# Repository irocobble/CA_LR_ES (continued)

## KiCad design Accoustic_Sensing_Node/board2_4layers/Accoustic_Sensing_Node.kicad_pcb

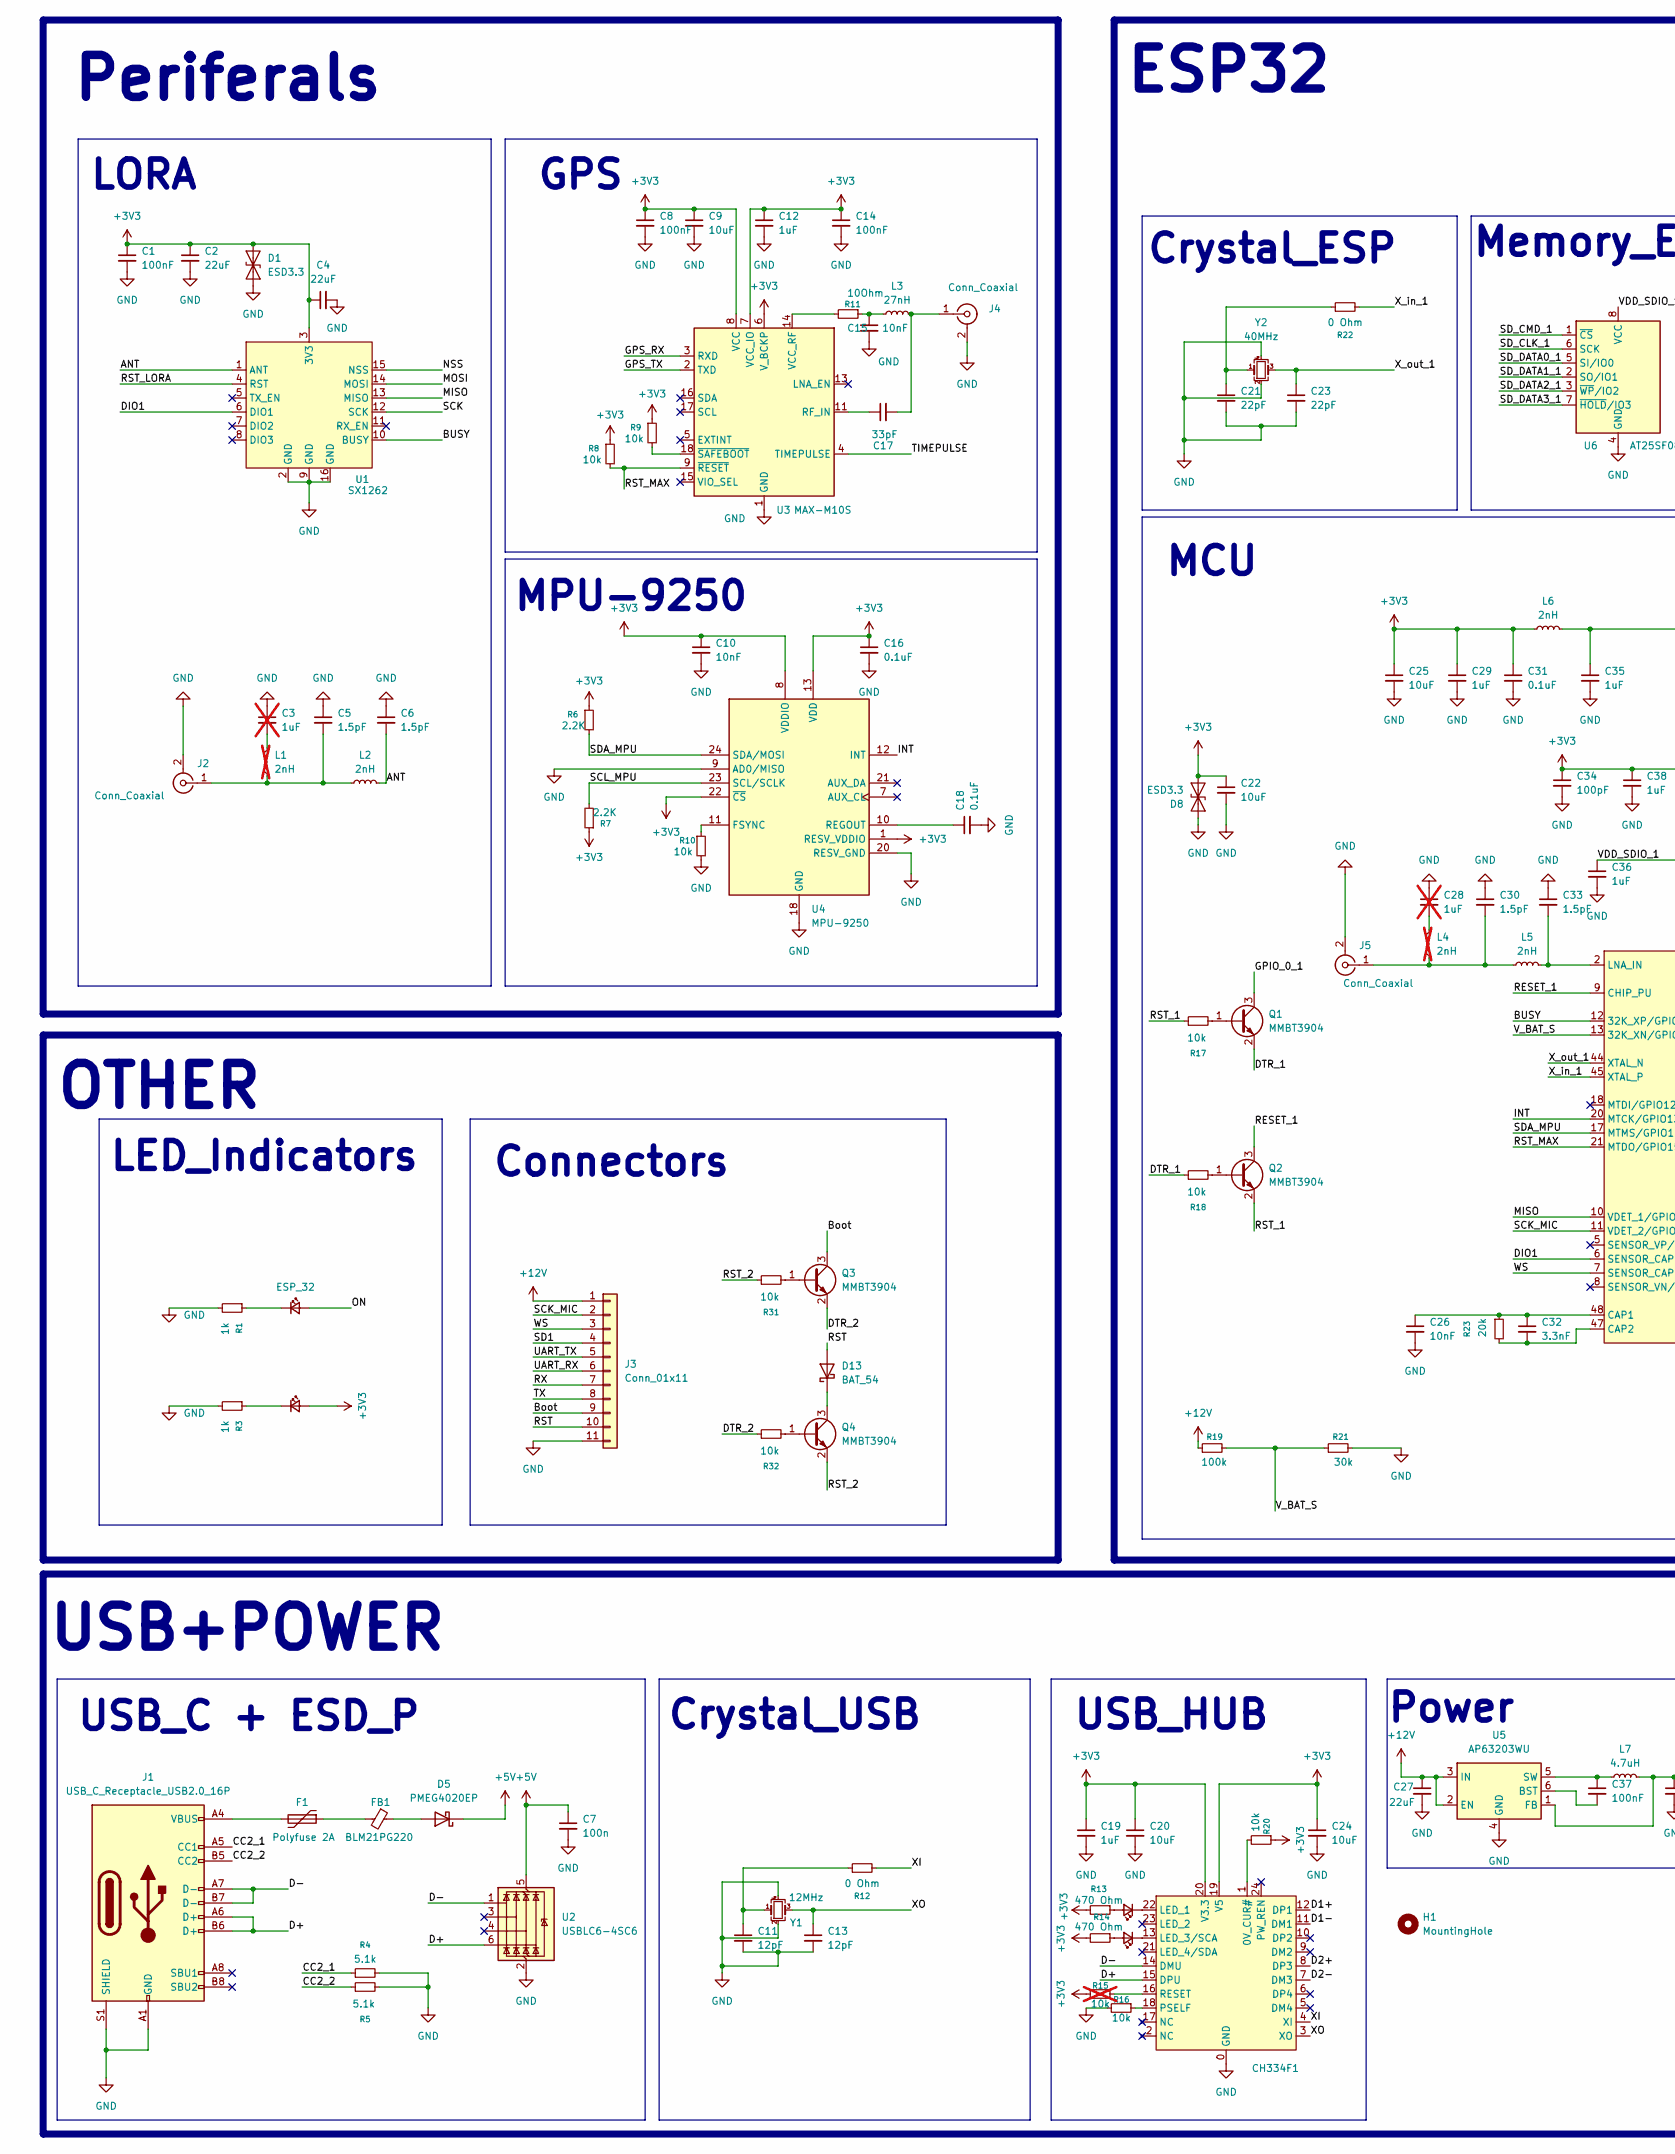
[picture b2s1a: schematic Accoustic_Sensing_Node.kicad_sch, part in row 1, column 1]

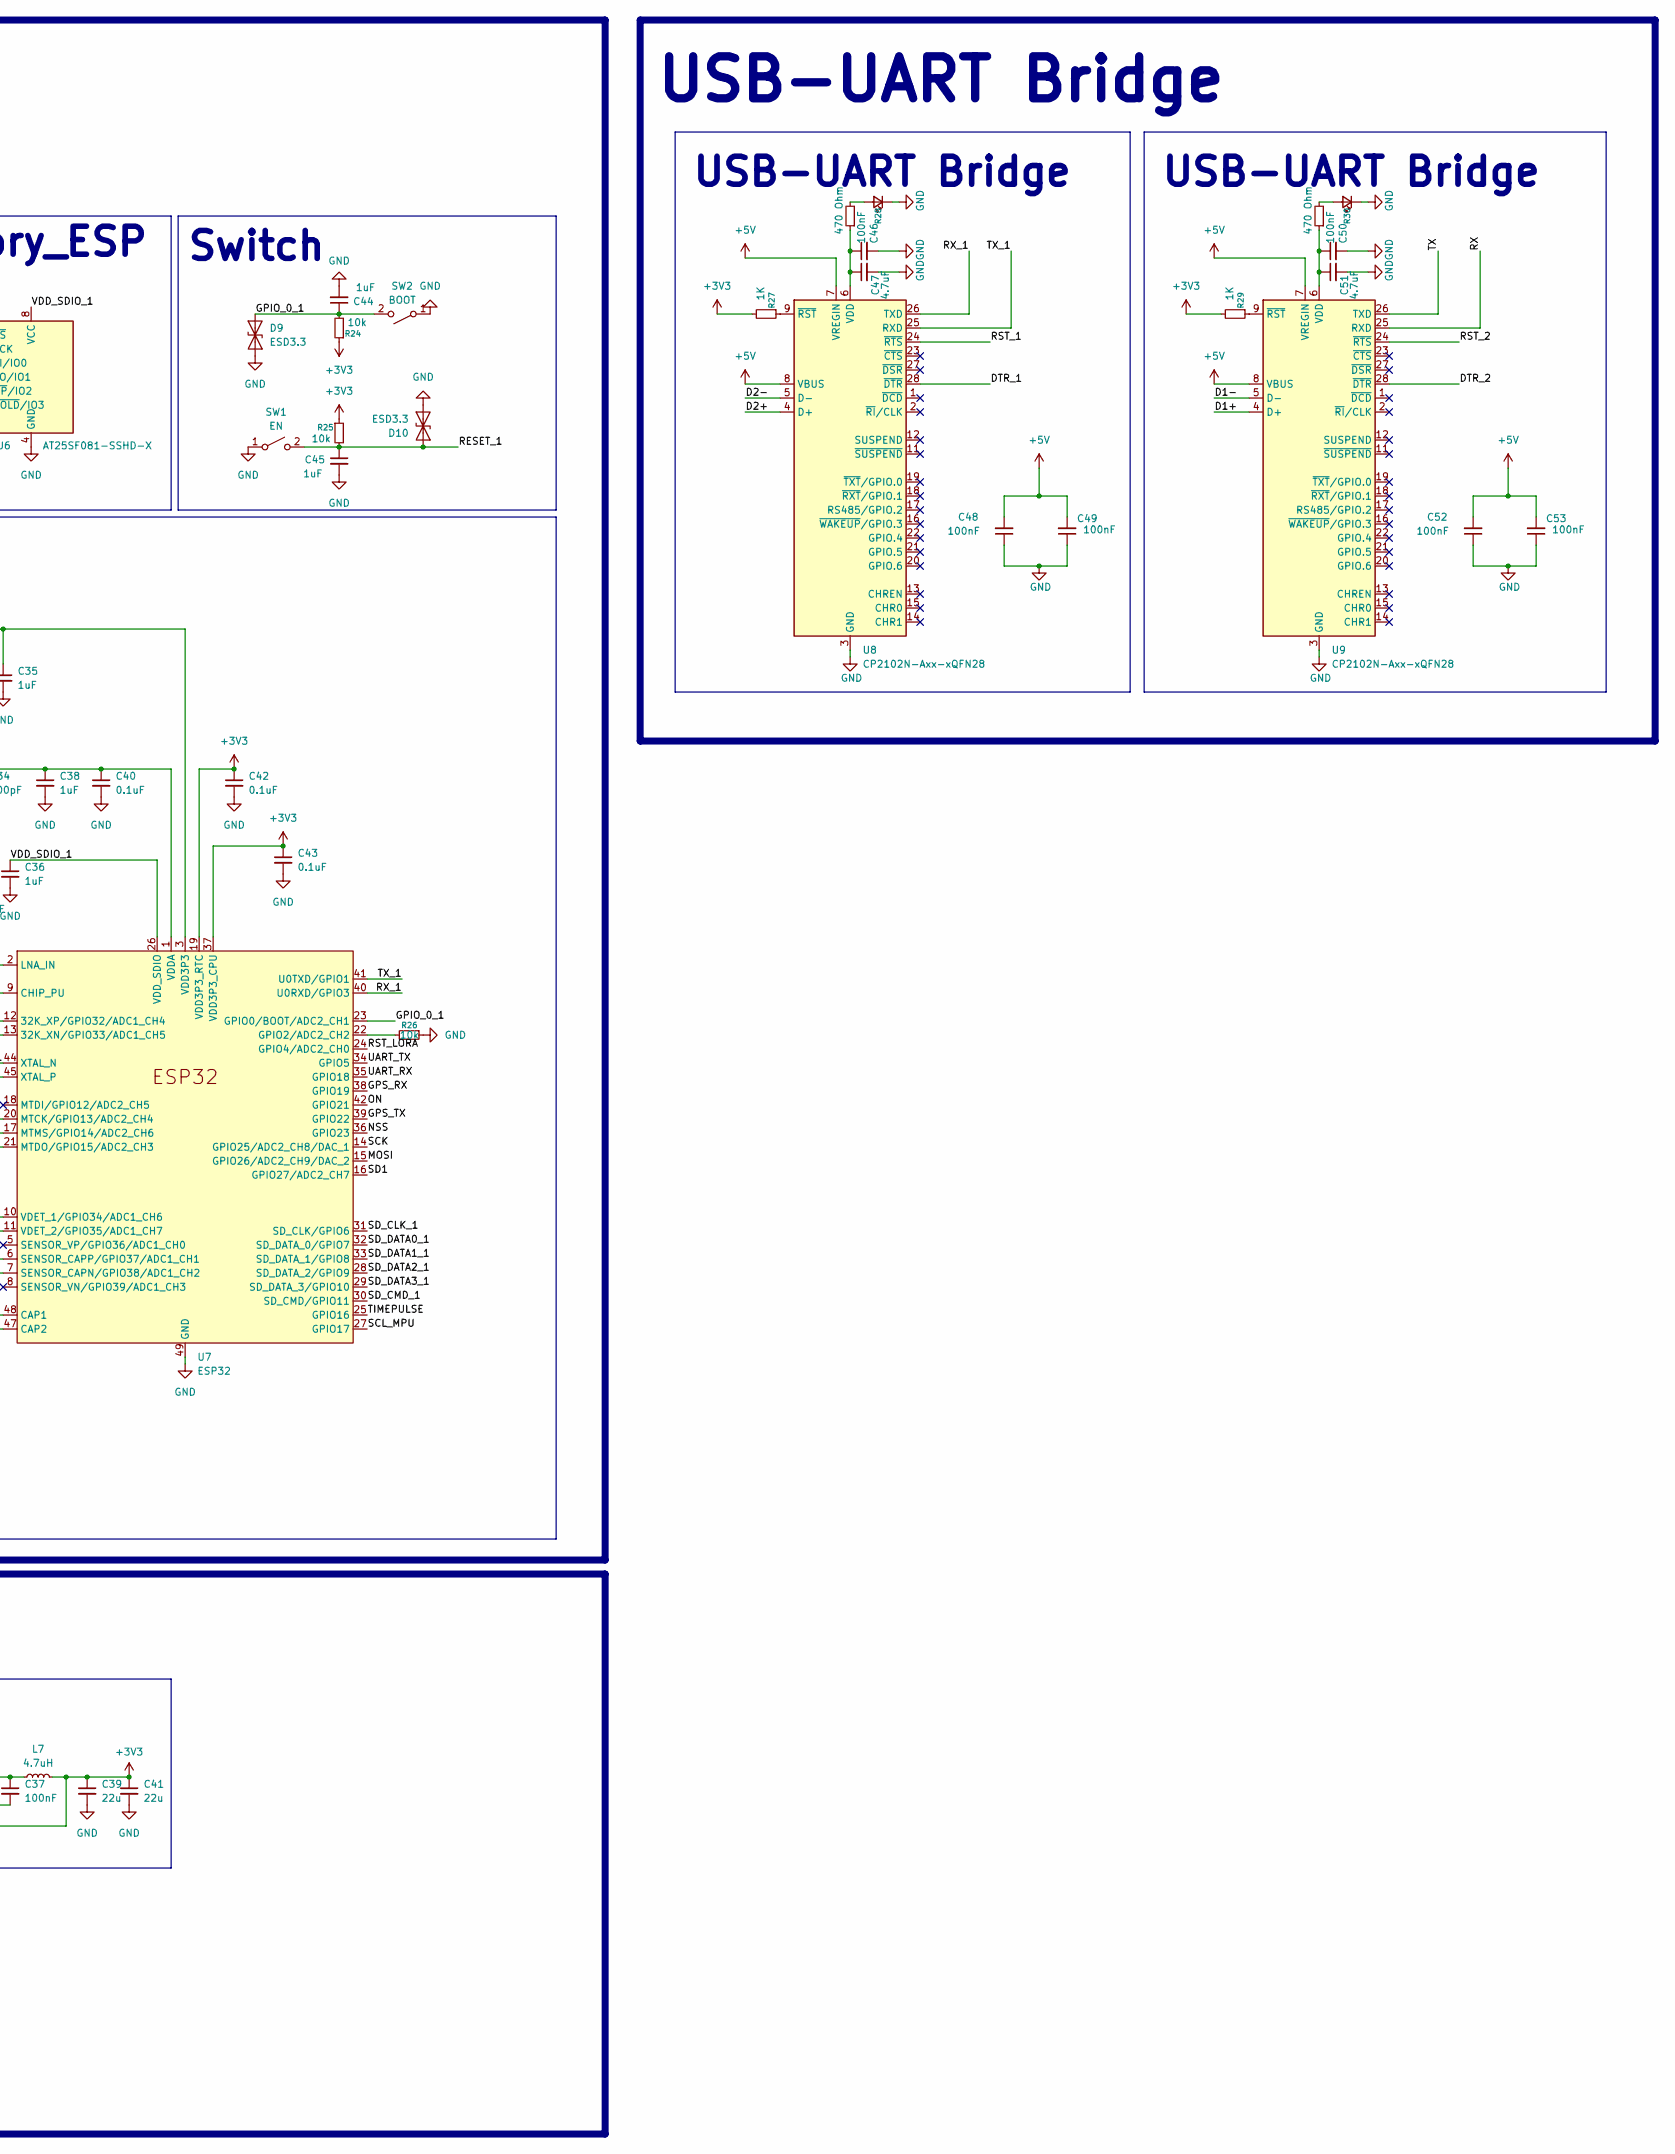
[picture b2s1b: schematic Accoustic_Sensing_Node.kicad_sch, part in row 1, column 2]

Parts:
C1, C8, C14, C37: 100nF; C_0603_1608Metric
C2, C4, C27: 22uF; C_0805_2012Metric
C3, C28: 1uF; C_0603_1608Metric; not fitted
C5, C6, C30, C33: 1.5pF; C_0402_1005Metric
C7: 100n; C_0402_1005Metric
C9, C20, C22, C24: 10uF; C_0805_2012Metric
C10, C15: 10nF; C_0603_1608Metric
C11, C13: 12pF; C_0402_1005Metric
C12: 1uF; C_0402_1005Metric
C16, C18, C31, C40, C42, C43: 0.1uF; C_0402_1005Metric
C17: 33pF; C_0402_1005Metric
C19, C29, C35, C36, C38, C44, C45: 1uF; C_0603_1608Metric
C21, C23: 22pF; C_0402_1005Metric
C25: 10uF; C_0805_2012Metric_Pad1.18x1.45mm_HandSolder
C26: 10nF; C_0402_1005Metric
C32: 3.3nF; C_0402_1005Metric
C34: 100pF; C_0402_1005Metric
C39, C41: 22u; C_0805_2012Metric
C46, C48, C49, C50, C52, C53: 100nF; C_0402_1005Metric
C47, C51: 4.7uF; C_0805_2012Metric
CH334F1: QFN24_4MM
D1, D8, D9, D10: ESD3.3; D_SOD-523
D2: ESP_32; LED_0805_2012Metric
D4: Power; LED_0805_2012Metric
D5: PMEG4020EP; D_SOD-123F
D6: USB1; LED_0805_2012Metric
D7: USB2; LED_0805_2012Metric
D11, D12: UART1_ON; LED_0805_2012Metric
D13: BAT_54; SOT-23
F1: Polyfuse 2A; Fuse_1206_3216Metric
FB1: BLM21PG220; L_0805_2012Metric
H1: MountingHole; MountingHole_2.7mm_M2.5_Pad_TopBottom
J1: USB_C_Receptacle_USB2.0_16P; USB_C_Receptacle_HCTL_HC-TYPE-C-16P-01A
J2, J4, J5: Conn_Coaxial; U.FL_Hirose_U.FL-R-SMT-1_Vertical
J3: Conn_01x11; Castellated_Edge_11P_2.54
L1, L4: 2nH; L_0402_1005Metric; not fitted
L2, L5, L6: 2nH; L_0402_1005Metric
L3: 27nH; L_0402_1005Metric
L7: 4.7uH; L_Sunlord_SWPA6020S
Q1, Q2, Q3, Q4: MMBT3904; SOT-23
R1, R3: 1k; R_0402_1005Metric
R4, R5: 5.1k; R_0402_1005Metric
R6, R7: 2.2K; R_0402_1005Metric
R8, R9, R10, R16, R17, R18, R20, R24, R25, R26, R31, R32: 10k; R_0402_1005Metric
R11: 10Ohm; R_0805_2012Metric
R12, R22: 0 Ohm; R_0402_1005Metric
R13, R14, R28, R30: 470 Ohm; R_0402_1005Metric
R15: 10k; R_0402_1005Metric; not fitted
R19: 100k; R_0402_1005Metric
R21: 30k; R_0402_1005Metric
R23: 20k; R_0402_1005Metric
R27, R29: 1K; R_0402_1005Metric
SW1: EN; SW_CS1213AGF260_CRS
SW2: BOOT; SW_CS1213AGF260_CRS
U1: SX1262; SX1262-B
U2: USBLC6-4SC6; SOT-23-6
U3: MAX-M10S; ublox_MAX
U4: MPU-9250; InvenSense_QFN-24_3x3mm_P0.4mm
U5: AP63203WU; TSOT-23-6
U6: AT25SF081-SSHD-X; SOIC-8_3.9x4.9mm_P1.27mm
U7: ESP32; QFN-48-1EP_5x5mm_P0.35mm_EP3.7x3.7mm
U8, U9: CP2102N-Axx-xQFN28; QFN-28-1EP_5x5mm_P0.5mm_EP3.35x3.35mm
Y1: 12MHz; Crystal_SMD_3225-4Pin_3.2x2.5mm
Y2: 40MHz; Crystal_SMD_3225-4Pin_3.2x2.5mm

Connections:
+3V3: C1.1, C2.1, C4.1, C8.1, C9.1, C10.1, C12.1, C14.1, C16.1, C19.1, C20.1, C22.1, C24.1, C25.1, C29.1, C31.1, C34.1, C38.1, C39.1, C40.1, C41.1, C42.1, C43.1, CH334F1.19 (V5), CH334F1.20 (V3.3), D1.2 (A2), D4.2 (A), D8.1 (A1), L6.1, L7.2, R6.1, R7.1, R8.1, R9.1, R13.2, R14.2, R15.2, R20.1, R24.1, R25.1, R27.2, R29.2, U1.3 (3V3), U3.6 (V_BCKP), U3.7 (VCC_IO), U3.8 (VCC), U4.1 (RESV_VDDIO), U4.8 (VDDIO), U4.13 (VDD), U4.22 (~CS), U5.1 (FB), U7.1 (VDDA), U7.19 (VDD3P3_RTC), U7.37 (VDD3P3_CPU), U7.43 (VDDA), U7.46 (VDDA)
+5V: C7.1, C48.2, C49.2, C52.2, C53.2, D5.1 (K), U2.5 (VBUS), U8.7 (VREGIN), U8.8 (VBUS), U9.7 (VREGIN), U9.8 (VBUS)
+12V: C27.1, J3.1, R19.1, U5.2 (EN), U5.3 (IN)
/ANT: C6.2, L2.2, U1.1 (ANT)
/BUSY: U1.10 (BUSY), U7.12 (32K_XP/GPIO32/ADC1_CH4)
/Boot: J3.9, Q3.3 (C)
/CC2_1: J1.A5 (CC1), R4.1
/CC2_2: J1.B5 (CC2), R5.1
/D1+: CH334F1.12 (DP1), U9.4 (D+)
/D1-: CH334F1.11 (DM1), U9.5 (D-)
/D2+: CH334F1.8 (DP3), U8.4 (D+)
/D2-: CH334F1.7 (DM3), U8.5 (D-)
/D+: CH334F1.15 (DPU), J1.A6 (D+), J1.B6 (D+), U2.6 (I/O4)
/D-: CH334F1.14 (DMU), J1.A7 (D-), J1.B7 (D-), U2.1 (I/O1)
/DIO1: U1.6 (DIO1), U7.6 (SENSOR_CAPP/GPIO37/ADC1_CH1)
/DTR_1: Q1.2 (E), R18.1, U8.28 (~DTR)
/DTR_2: Q3.2 (E), R32.1, U9.28 (~DTR)
/GPIO_0_1: C44.1, D9.2 (A2), Q1.3 (C), R24.2, SW2.2 (B), U7.23 (GPIO0/BOOT/ADC2_CH1)
/GPS_RX: U3.3 (RXD), U7.38 (GPIO19)
/GPS_TX: U3.2 (TXD), U7.39 (GPIO22)
/INT: U4.12 (INT), U7.20 (MTCK/GPIO13/ADC2_CH4)
/MISO: U1.13 (MISO), U7.10 (VDET_1/GPIO34/ADC1_CH6)
/MOSI: U1.14 (MOSI), U7.15 (GPIO26/ADC2_CH9/DAC_2)
/NSS: U1.15 (NSS), U7.36 (GPIO23)
/ON: D2.2 (A), U7.42 (GPIO21)
/RESET_1: C45.1, D10.2 (A2), Q2.3 (C), R25.2, SW1.2 (B), U7.9 (CHIP_PU)
/RST: D13.2 (A), J3.10
/RST_1: Q2.2 (E), R17.1, U8.24 (~RTS)
/RST_2: Q4.2 (E), R31.1, U9.24 (~RTS)
/RST_LORA: U1.4 (RST), U7.24 (GPIO4/ADC2_CH0)
/RST_MAX: R8.2, U3.9 (~RESET), U7.21 (MTDO/GPIO15/ADC2_CH3)
/RX: J3.7, U9.25 (RXD)
/RX_1: U7.40 (U0RXD/GPIO3), U8.26 (TXD)
/SCK: U1.12 (SCK), U7.14 (GPIO25/ADC2_CH8/DAC_1)
/SCK_MIC: J3.2, U7.11 (VDET_2/GPIO35/ADC1_CH7)
/SCL_MPU: R7.2, U4.23 (SCL/SCLK), U7.27 (GPIO17)
/SD1: J3.4, U7.16 (GPIO27/ADC2_CH7)
/SDA_MPU: R6.2, U4.24 (SDA/MOSI), U7.17 (MTMS/GPIO14/ADC2_CH6)
/SD_CLK_1: U6.6 (SCK), U7.31 (SD_CLK/GPIO6)
/SD_CMD_1: U6.1 (~CS), U7.30 (SD_CMD/GPIO11)
/SD_DATA0_1: U6.5 (SI/IO0), U7.32 (SD_DATA_0/GPIO7)
/SD_DATA1_1: U6.2 (SO/IO1), U7.33 (SD_DATA_1/GPIO8)
/SD_DATA2_1: U6.3 (~WP/IO2), U7.28 (SD_DATA_2/GPIO9)
/SD_DATA3_1: U6.7 (~HOLD/IO3), U7.29 (SD_DATA_3/GPIO10)
/TIMEPULSE: U3.4 (TIMEPULSE), U7.25 (GPIO16)
/TX: J3.8, U9.26 (TXD)
/TX_1: U7.41 (U0TXD/GPIO1), U8.25 (RXD)
/UART_RX: J3.6, U7.35 (GPIO18)
/UART_TX: J3.5, U7.34 (GPIO5)
/VDD_SDIO_1: C36.1, U6.8 (VCC), U7.26 (VDD_SDIO)
/V_BAT_S: R19.2, R21.1, U7.13 (32K_XN/GPIO33/ADC1_CH5)
/WS: J3.3, U7.7 (SENSOR_CAPN/GPIO38/ADC1_CH2)
/XI: CH334F1.4 (XI), R12.2
/XO: C13.1, CH334F1.3 (XO), Y1.3
/X_in_1: R22.2, U7.45 (XTAL_P)
/X_out_1: C23.1, U7.44 (XTAL_N), Y2.3
GND: C1.2, C2.2, C3.1, C4.2, C5.1, C6.1, C7.2, C8.2, C9.2, C10.2, C11.2, C12.2, C13.2, C14.2, C15.2, C16.2, C18.2, C19.2, C20.2, C21.2, C22.2, C23.2, C24.2, C25.2, C26.2, C27.2, C28.1, C29.2, C30.1, C31.2, C33.1, C34.2, C35.2, C36.2, C38.2, C39.2, C40.2, C41.2, C42.2, C43.2, C44.2, C45.2, C46.2, C47.2, C48.1, C49.1, C50.2, C51.2, C52.1, C53.1, CH334F1.0 (GND), D1.1 (A1), D8.2 (A2), D9.1 (A1), D10.1 (A1), D11.1 (K), D12.1 (K), J1.A1 (GND), J1.A12 (GND), J1.B1 (GND), J1.B12 (GND), J1.S1 (SHIELD), J2.2 (Ext), J3.11, J4.2 (Ext), J5.2 (Ext), R1.2, R3.2, R4.2, R5.2, R10.2, R16.2, R21.2, R26.1, SW1.1 (A), SW2.1 (A), U1.2 (GND), U1.9 (GND), U1.16 (GND), U2.2 (GND), U3.1 (GND), U3.10 (GND), U3.12 (GND), U4.9 (AD0/MISO), U4.18 (GND), U4.20 (RESV_GND), U5.4 (GND), U6.4 (GND), U7.49 (GND), U8.3 (GND), U8.29 (GND), U9.3 (GND), U9.29 (GND), Y1.2, Y1.4, Y2.2, Y2.4
unnamed: C3.2, L1.2
unnamed: C11.1, R12.1, Y1.1
unnamed: C15.1, L3.1, R11.1
unnamed: C21.1, R22.1, Y2.1
unnamed: C28.2, L4.2
unnamed: C35.1, L6.2, U7.3 (VDD3P3), U7.4 (VDD3P3)
unnamed: CH334F1.1 (0V_CUR#), R20.2
unnamed: CH334F1.22 (LED_1), D6.1 (K)
unnamed: CH334F1.13 (LED_3/SCA), D7.1 (K)
unnamed: CH334F1.18 (PSELF), R16.1
unnamed: CH334F1.16 (RESET), R15.1
unnamed: D2.1 (K), R1.1
unnamed: D4.1 (K), R3.1
unnamed: D5.2 (A), FB1.1
unnamed: D6.2 (A), R13.1
unnamed: D7.2 (A), R14.1
unnamed: D11.2 (A), R28.2
unnamed: D12.2 (A), R30.2
unnamed: D13.1 (K), Q4.3 (C)
unnamed: F1.1, FB1.2
unnamed: F1.2, J1.A4 (VBUS), J1.A9 (VBUS), J1.B4 (VBUS), J1.B9 (VBUS)
unnamed: C5.2, J2.1 (In), L1.1, L2.1
unnamed: C17.2, J4.1 (In), L3.2
unnamed: C30.2, J5.1 (In), L4.1, L5.1
unnamed: Q1.1 (B), R17.2
unnamed: Q2.1 (B), R18.2
unnamed: Q3.1 (B), R31.2
unnamed: Q4.1 (B), R32.2
unnamed: C17.1, U3.11 (RF_IN)
unnamed: R11.2, U3.14 (VCC_RF)
unnamed: R9.2, U3.18 (~SAFEBOOT)
unnamed: R10.1, U4.11 (FSYNC)
unnamed: C18.1, U4.10 (REGOUT)
unnamed: C37.2, U5.6 (BST)
unnamed: C37.1, L7.1, U5.5 (SW)
unnamed: C26.1, C32.1, R23.1, U7.48 (CAP1)
unnamed: C32.2, R23.2, U7.47 (CAP2)
unnamed: R26.2, U7.22 (GPIO2/ADC2_CH2)
unnamed: C33.2, L5.2, U7.2 (LNA_IN)
unnamed: C46.1, C47.1, R28.1, U8.6 (VDD)
unnamed: R27.1, U8.9 (~RST)
unnamed: C50.1, C51.1, R30.1, U9.6 (VDD)
unnamed: R29.1, U9.9 (~RST)

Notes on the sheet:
Switch
OTHER
MPU-9250
Power
MCU
USB-UART Bridge
Crystal_ESP
GPS
USB+POWER
Crystal_USB
ESP32
Memory_ESP
LED_Indicators
USB_HUB
Connectors
USB_C + ESD_P
Periferals
LORA

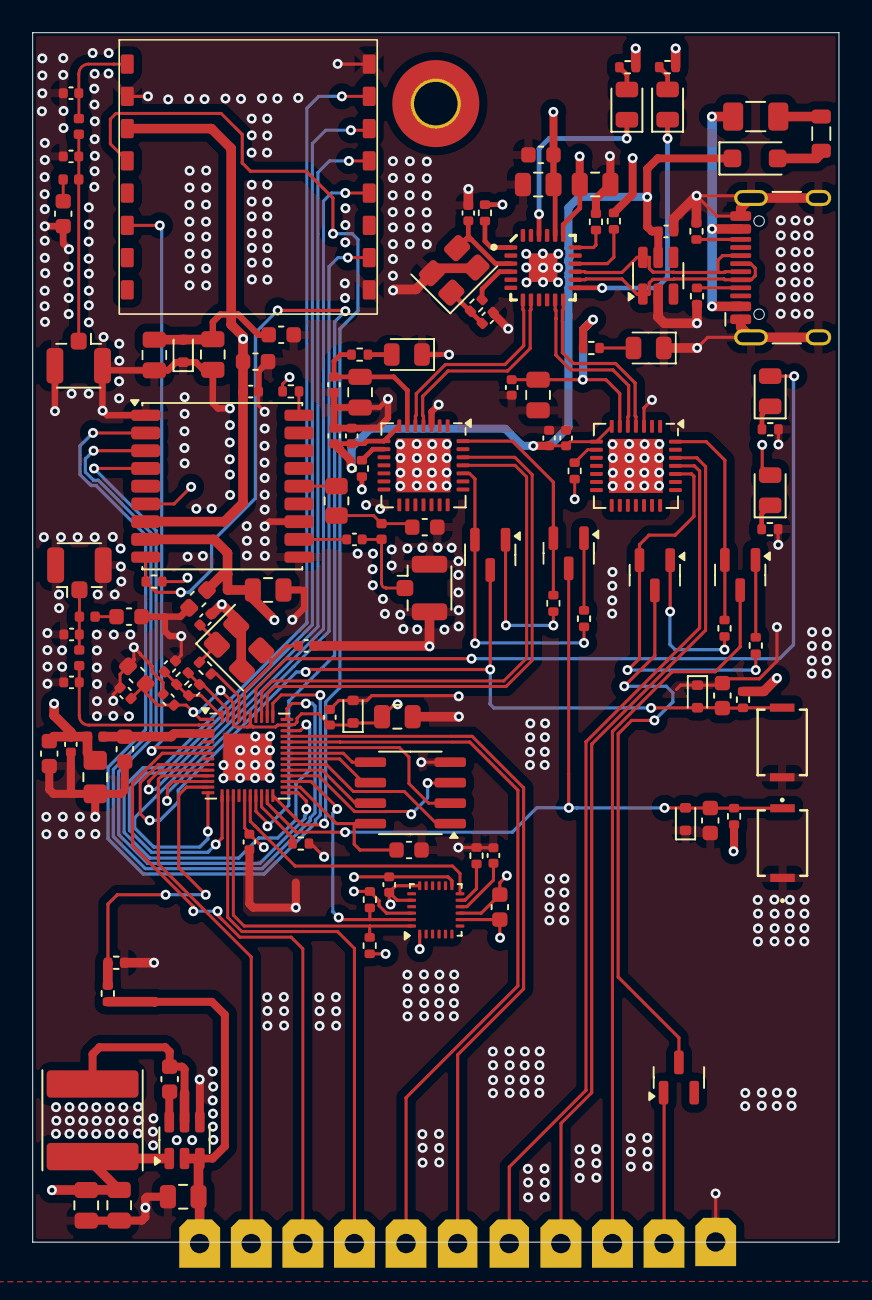
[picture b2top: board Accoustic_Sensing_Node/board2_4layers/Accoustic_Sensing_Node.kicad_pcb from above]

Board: 4 copper layers, 50.0 x 75.0 mm, 129 parts (0 on the bottom side), 100 nets.

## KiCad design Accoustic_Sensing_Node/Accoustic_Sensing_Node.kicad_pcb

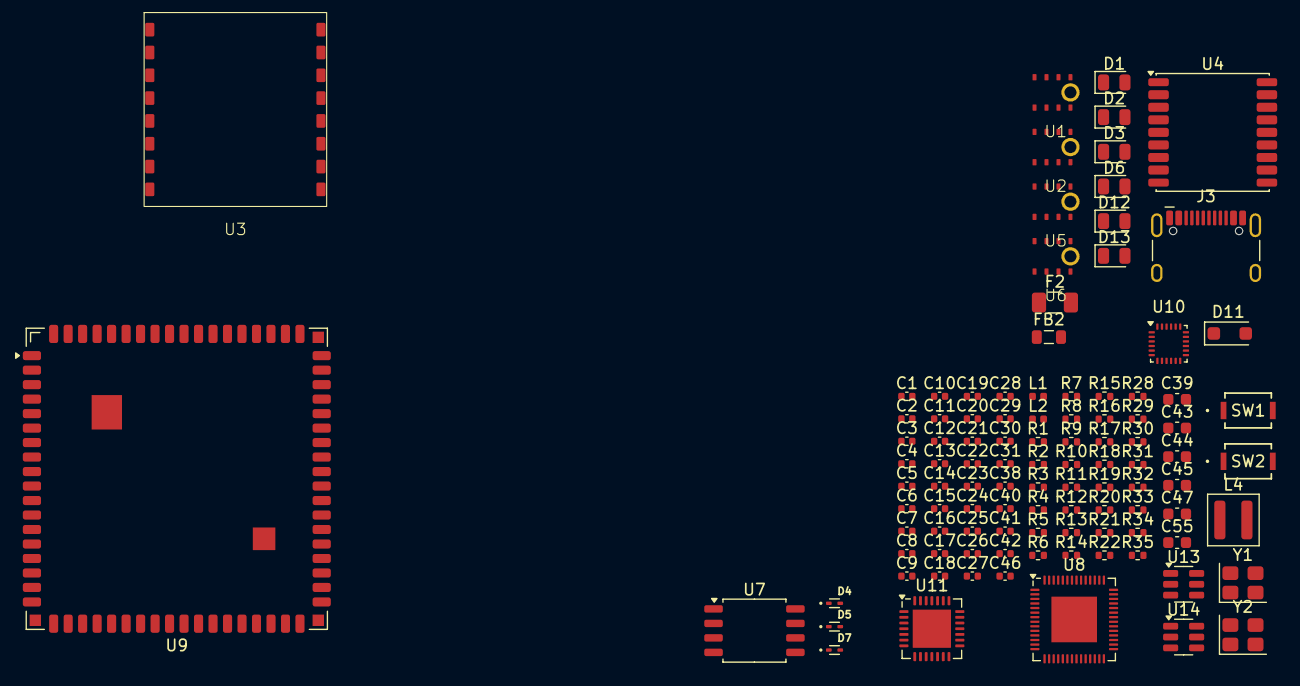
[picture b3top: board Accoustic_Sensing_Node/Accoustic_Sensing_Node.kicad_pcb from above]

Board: 2 copper layers, 105 parts (0 on the bottom side), 65 nets, no tracks yet.

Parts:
C1, C2, C10, C11, C16, C17, C18, C19, C20, C22, C24, C30, C31, C46: 0.1uF; C_0402_1005Metric
C3, C5, C8, C21, C27, C28, C42: 100nF; C_0402_1005Metric
C4, C13: 10uF; C_0402_1005Metric
C6, C7, C15, C25, C26: 1uF; C_0402_1005Metric
C9, C23, C29: 10nF; C_0402_1005Metric
C12, C14: 30pF; C_0402_1005Metric
C38: 100n; C_0402_1005Metric
C39, C47: 10uF; C_0603_1608Metric
C40, C41: 12pF; C_0402_1005Metric
C43, C44: 22u; C_0603_1608Metric
C45: 1uF; C_0603_1608Metric
C55: 4.7uF; C_0603_1608Metric
D1: LORA_ON; LED_0805_2012Metric
D2: LORA_OFF; LED_0805_2012Metric
D3: Power; LED_0805_2012Metric
D4, D5, D7: ESD3.3; SODFL1006X40N
D6: UART1_ON; LED_0805_2012Metric
D11: PMEG4020EP; D_SOD-123F
D12: USB1; LED_0805_2012Metric
D13: USB2; LED_0805_2012Metric
F2: Polyfuse 2A; Fuse_1206_3216Metric
FB2: BLM21PG220; L_0805_2012Metric
J3: USB_C_Receptacle_USB2.0_16P; USB_C_Receptacle_HCTL_HC-TYPE-C-16P-01A
L1: 27nH; L_0402_1005Metric
L2: 2nH; L_0402_1005Metric
L4: 4.7uH; L_Coilcraft_XAL4030-XXX
R1, R2, R6, R7, R9, R10, R12, R20, R33, R34, R35: 10k; R_0402_1005Metric
R3, R4, R14, R31, R32: 470 Ohm; R_0402_1005Metric
R5: 1k; R_0402_1005Metric
R8: 10Ohm; R_0402_1005Metric
R11: 100 Ohm; R_0402_1005Metric
R13: 1K; R_0402_1005Metric
R15, R16, R17, R18, R19: 0kOhm; R_0402_1005Metric
R21, R22: 2.2K; R_0402_1005Metric
R28, R29: 5.1k; R_0402_1005Metric
R30: 0 Ohm; R_0402_1005Metric
SW1: BOOT; SW_CS1213AGF260_CRS
SW2: Reset; SW_CS1213AGF260_CRS
U1: MIC1; INMP441
U2: MIC3; INMP441
U3: SX1262; SX1262-B
U4: MAX-M10S; ublox_MAX
U5: MIC2; INMP441
U6: MIC4; INMP441
U7: W25Q128JVS; SOIC-8_5.3x5.3mm_P1.27mm
U8: ESP32-S3; QFN-56-1EP_7x7mm_P0.4mm_EP4x4mm
U9: Sipeed-M1
U10: MPU-9250; InvenSense_QFN-24_3x3mm_P0.4mm
U11: CP2102N-Axx-xQFN28; QFN-28-1EP_5x5mm_P0.5mm_EP3.35x3.35mm
U13: USBLC6-4SC6; SOT-23-6
U14: AP63203WU; TSOT-23-6
Y1: 40MHz; Crystal_SMD_3225-4Pin_3.2x2.5mm
Y2: 12MHz; Crystal_SMD_3225-4Pin_3.2x2.5mm

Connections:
+5V: C27.2, C28.2, C38.1, C39.1, D11.1 (K), U11.7 (VREGIN), U11.8 (VBUS), U13.5 (VBUS), U14.2 (EN), U14.3 (IN)
/BUSY: U3.10 (BUSY), U8.14 (GPIO9)
/CC2_1: J3.A5 (CC1), R28.1
/CC2_2: J3.B5 (CC2), R29.1
/D+: J3.A6 (D+), J3.B6 (D+), U13.6 (I/O4)
/D-: J3.A7 (D-), J3.B7 (D-), U13.1 (I/O1)
/DIO1: U3.6 (DIO1), U8.15 (GPIO10)
/LED_LORA_Green: D1.2 (A), U3.7 (DIO2)
/LED_LORA_red: D2.2 (A), U3.8 (DIO3)
/MISO: U3.13 (MISO), U8.12 (GPIO7)
/MOSI: U3.14 (MOSI), U8.11 (GPIO6)
/NSS: U3.15 (NSS), U8.9 (GPIO4)
/SCK: U3.12 (SCK), U8.10 (GPIO5)
/SCK_MIC: U1.1 (SCK), U2.1 (SCK), U5.1 (SCK), U6.1 (SCK), U8.19 (GPIO14)
/SD_1: U1.2 (SD), U5.2 (SD), U8.18 (GPIO13)
/SD_2: U2.2 (SD), U6.2 (SD), U8.17 (GPIO12)
/WS: U1.3 (WS), U2.3 (WS), U5.3 (WS), U6.3 (WS), U8.16 (GPIO11)
/XO: C41.1, Y2.3
/X_in_1: R11.2, U8.54 (XTAL_P)
/X_out_1: C14.1, U8.53 (XTAL_N), Y1.3
GND: C1.2, C2.2, C3.2, C4.2, C5.2, C6.2, C7.2, C8.2, C9.2, C10.2, C11.2, C12.2, C13.2, C14.2, C15.2, C16.2, C17.2, C18.2, C19.2, C20.2, C21.2, C22.2, C23.2, C24.2, C25.2, C26.2, C27.1, C28.1, C29.2, C30.2, C31.2, C38.2, C39.2, C40.2, C41.2, C43.2, C44.2, C45.2, C46.2, C47.2, C55.2, D4.1 (A1), D5.1 (A1), D6.1 (K), D7.1 (A1), J3.A1 (GND), J3.A12 (GND), J3.B1 (GND), J3.B12 (GND), J3.S1 (SHIELD), R3.2, R4.2, R5.2, R28.2, R29.2, R34.2, SW1.1 (A), SW2.1 (A), U1.4 (L/R), U1.5 (GND), U1.8 (GND), U2.4 (L/R), U2.5 (GND), U2.8 (GND), U3.2 (GND), U3.9 (GND), U3.16 (GND), U4.1 (GND), U4.10 (GND), U4.12 (GND), U5.5 (GND), U5.8 (GND), U6.5 (GND), U6.8 (GND), U7.4 (GND), U8.57 (GND), U10.18 (GND), U10.20 (RESV_GND), U11.3 (GND), U11.29 (GND), U13.2 (GND), U14.4 (GND), Y1.2, Y1.4, Y2.2, Y2.4
unnamed: C9.1, L1.2, R8.2
unnamed: C12.1, R11.1, Y1.1
unnamed: C18.1, L2.2, U8.2 (VDD3P3), U8.3 (VDD3P3)
unnamed: C40.1, R30.1, Y2.1
unnamed: D1.1 (K), R3.1
unnamed: D2.1 (K), R4.1
unnamed: D3.1 (K), R5.1
unnamed: C17.1, D5.2 (A2), R12.2, SW1.2 (B), U8.5 (GPIO0)
unnamed: D6.2 (A), R14.2
unnamed: C24.1, D7.2 (A2), R20.2, SW2.2 (B), U8.4 (CHIP_PU)
unnamed: D11.2 (A), FB2.1
unnamed: D12.2 (A), R31.1
unnamed: D13.2 (A), R32.1
unnamed: F2.1, FB2.2
unnamed: F2.2, J3.A4 (VBUS), J3.A9 (VBUS), J3.B4 (VBUS), J3.B9 (VBUS)
unnamed: R1.2, U1.7 (EN)
unnamed: R2.2, U2.7 (EN)
unnamed: L1.1, U4.14 (VCC_RF)
unnamed: R7.2, U4.6 (V_BCKP)
unnamed: R6.2, U4.9 (~RESET)
unnamed: R9.2, U5.7 (EN)
unnamed: R10.2, U6.7 (EN)
unnamed: R17.2, U8.33 (SPICLK)
unnamed: R19.2, U8.35 (SPID)
unnamed: R15.2, U8.30 (SPIHD)
unnamed: R18.2, U8.34 (SPIQ)
unnamed: R16.2, U8.31 (SPIWP)
unnamed: U9.51 (5V), U9.52 (5V)
unnamed: U9.49 (GND), U9.50 (GND), U9.72 (GND)
unnamed: C30.1, U10.10 (REGOUT)
unnamed: R22.2, U10.23 (SCL/SCLK)
unnamed: R21.2, U10.24 (SDA/MOSI)
unnamed: C21.1, C55.1, R14.1, U11.6 (VDD)
unnamed: R13.1, U11.9 (~RST)
unnamed: C42.2, U14.6 (BST)
unnamed: C42.1, L4.1, U14.5 (SW)
SPICS0: U7.1 (~CS), U8.32 (SPICS0)
SPID: R19.1, U7.5 (DI/IO_{0})
SPIHD: R15.1, U7.7 (~HOLD/~RESET/IO_{3})
SPIQ: R18.1, U7.2 (DO/IO_{1})
SPISCK: R17.1, U7.6 (CLK)
SPIWP: R16.1, U7.3 (~WP/IO_{2})
VDD_CPU: C1.1, C2.1, C3.1, C4.1, C5.1, C6.1, C7.1, C8.1, C10.1, C11.1, C13.1, C15.1, C16.1, C19.1, C20.1, C23.1, C26.1, C29.1, C31.1, C43.1, C44.1, C45.1, C46.1, C47.1, D3.2 (A), D4.2 (A2), L2.1, L4.2, R1.1, R2.1, R6.1, R7.1, R9.1, R10.1, R12.1, R13.2, R20.1, R21.1, R22.1, R31.2, R32.2, R33.2, R35.1, U1.6 (VDD), U2.6 (VDD), U3.3 (3V3), U4.7 (VCC_IO), U4.8 (VCC), U5.4 (L/R), U5.6 (VDD), U6.4 (L/R), U6.6 (VDD), U8.20 (VDD3P3_RTC), U8.46 (VDD3P3_CPU), U8.55 (VDDA), U8.56 (VDDA), U10.8 (VDDIO), U10.13 (VDD), U10.22 (~CS), U14.1 (FB)
VDD_SPI: C22.1, C25.1, U7.8 (VCC), U8.29 (VDD_SPI)

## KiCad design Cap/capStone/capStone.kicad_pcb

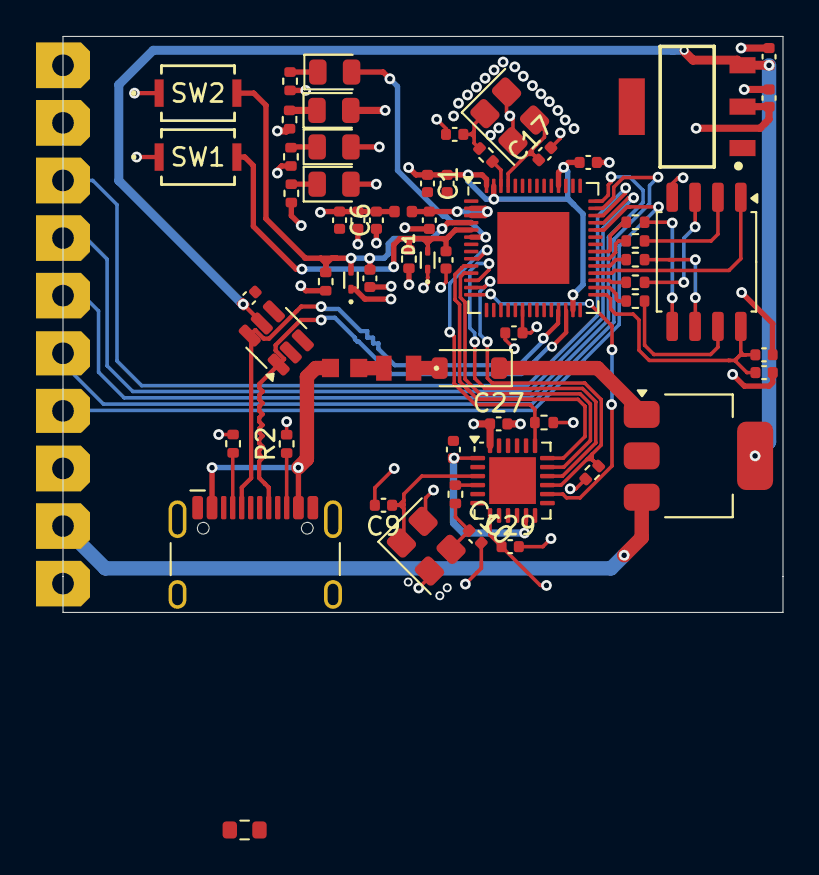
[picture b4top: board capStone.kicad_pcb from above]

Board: 4 copper layers, 40.0 x 32.0 mm, 62 parts (0 on the bottom side), 51 nets.

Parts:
C1: 10nF; C_0402_1005Metric
C2, C5, C12, C27, C29: 1uF; C_0402_1005Metric
C3, C4, C7, C11, C13, C24, C25: 0.1uF; C_0402_1005Metric
C6, C8: 10uF; C_0402_1005Metric
C9, C10, C16, C17: 30pF; C_0402_1005Metric
C22, C23: 22u; C_0402_1005Metric
C41: 100n; C_0402_1005Metric
D1, D2: ESD3.3; SODFL1006X40N
D3, D5, D67: Green; LED_0805_2012Metric
D4: BAT120C; SOT-223
D6: RED; LED_0805_2012Metric
D65: 1N5817; D_SOD-123
F1: Polyfuse 1A; FUSC1608X100N
FB1: BLM21PG220; IND_BLM21_MUR-L
J1: USB_C_Receptacle_USB2.0_16P; USB_C_Receptacle_HCTL_HC-TYPE-C-16P-01A
J4: Conn_01x10_Pin; Untitled
L1: 2nH; L_0402_1005Metric
R1, R2: 5.1k Ohm; R_0402_1005Metric
R3, R10, R12, R13: 10k; R_0402_1005Metric
R4, R9: 100 Ohm; R_0402_1005Metric
R8: 10k; R_0603_1608Metric
R14, R15, R21: 470 Ohm; R_0402_1005Metric
R16, R17, R18, R19, R20: 0kOhm; R_0402_1005Metric
R23: 1k Ohm; R_0402_1005Metric
SW1: BOOT; SW_CS1213AGF260_CRS
SW2: Reset; SW_CS1213AGF260_CRS
U1: ESP32-S3; QFN-56-1EP_7x7mm_P0.4mm_EP4x4mm
U2: SX1262IMLTRT; QFN-24-1EP_4x4mm_P0.5mm_EP2.6x2.6mm
U4: LM1117MP-3.3V; DCY0004A_L
U5: W25Q128JVS; SOIC-8_5.3x5.3mm_P1.27mm
U6: USBLC6-4SC6; SOT-23-6
Y1: 32MHz; Crystal_SMD_3225-4Pin_3.2x2.5mm
Y2: 40MHz; Crystal_SMD_3225-4Pin_3.2x2.5mm

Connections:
+5: C22.1, C41.1, D4.4 (K), U4.3 (VI), U6.5 (VBUS)
/BUSY: U1.14 (GPIO9), U2.14 (BUSY)
/CC2_1: J1.A5 (CC1), R1.1
/CC2_2: J1.B5 (CC2), R2.1
/D_1_C+: J1.A6 (D+), J1.B6 (D+), U1.26 (GPIO20/USB_D+), U6.1 (I/O1)
/D_1_C-: J1.A7 (D-), J1.B7 (D-), U1.25 (GPIO19/USB_D-), U6.6 (I/O4)
/GPIO4: R10.2, U1.9 (GPIO4), U2.19 (NSS)
/GPIO33: J4.7, U1.38 (GPIO33)
/GPIO34: J4.4, U1.39 (GPIO34)
/GPIO35: J4.3, U1.40 (GPIO35)
/GPIO36: J4.6, U1.41 (GPIO36)
/GPIO37: J4.5, U1.42 (GPIO37)
/LED_LORA_Green: D5.2 (A), U2.13 (DIO1)
/LED_LORA_red: D6.2 (A), U2.12 (DIO2)
/MISO: U1.12 (GPIO7), U2.16 (MISO)
/MOSI: U1.11 (GPIO6), U2.17 (MOSI)
/RESET: R3.2, U1.13 (GPIO8), U2.15 (~RESET)
/SCK: U1.10 (GPIO5), U2.18 (SCK)
/USB_+5V: D4.1 (A1), D65.1 (K), R8.1
/VIN: D4.3 (A2), J4.9
/X_in: C9.1, U2.3 (XTA), Y1.1
/X_in_1: R9.2, U1.54 (XTAL_P)
/X_out: R4.2, U2.4 (XTB)
/X_out_1: C17.1, U1.53 (XTAL_N), Y2.3
GND: C1.2, C2.2, C3.2, C4.2, C5.2, C6.2, C7.2, C8.2, C9.2, C10.2, C11.2, C12.2, C13.2, C16.2, C17.2, C22.2, C23.2, C24.2, C25.2, C27.2, C29.2, C41.2, D1.1 (A1), D2.1 (A1), J1.A1 (GND), J1.A12 (GND), J1.B1 (GND), J1.B12 (GND), J1.S1 (SHIELD), J4.2, J4.10, R1.2, R2.2, R8.2, R14.2, R15.2, R21.2, R23.2, SW1.1 (A), SW2.1 (A), U1.57 (GND), U2.2 (GND), U2.5 (GND), U2.8 (GND), U2.20 (GND), U2.25 (GND), U4.1 (GND), U5.4 (GND), U6.2 (GND), Y1.2, Y1.4, Y2.2, Y2.4
LED_ON: D3.2 (A), U1.6 (GPIO1)
unnamed: C4.1, L1.2, U1.2 (VDD3P3), U1.3 (VDD3P3)
unnamed: C10.1, R4.1, Y1.3
unnamed: C16.1, R9.1, Y2.1
unnamed: C25.1, D1.2 (A2), R13.2, SW1.2 (B), U1.5 (GPIO0)
unnamed: C24.1, D2.2 (A2), R12.2, SW2.2 (B), U1.4 (CHIP_PU)
unnamed: D3.1 (K), R14.1
unnamed: D5.1 (K), R15.1
unnamed: D6.1 (K), R21.1
unnamed: D65.2 (A), FB1.1
unnamed: D67.1 (K), R23.1
unnamed: F1.1, FB1.2
unnamed: F1.2, J1.A4 (VBUS), J1.A9 (VBUS), J1.B4 (VBUS), J1.B9 (VBUS)
unnamed: R16.2, U1.33 (SPICLK)
unnamed: R18.2, U1.35 (SPID)
unnamed: R20.2, U1.30 (SPIHD)
unnamed: R17.2, U1.34 (SPIQ)
unnamed: R19.2, U1.31 (SPIWP)
SPICS0: U1.32 (SPICS0), U5.1 (~CS)
SPID: R18.1, U5.5 (DI/IO_{0})
SPIHD: R20.1, U5.7 (~HOLD/~RESET/IO_{3})
SPIQ: R17.1, U5.2 (DO/IO_{1})
SPISCK: R16.1, U5.6 (CLK)
SPIWP: R19.1, U5.3 (~WP/IO_{2})
VDD_CPU: C1.1, C2.1, C3.1, C5.1, C6.1, C7.1, C8.1, C11.1, C23.1, C27.1, C29.1, D67.2 (A), J4.1, J4.8, L1.1, R3.1, R10.1, R12.1, R13.1, U1.20 (VDD3P3_RTC), U1.27 (GPIO21), U1.46 (VDD3P3_CPU), U1.55 (VDDA), U1.56 (VDDA), U2.1 (VDD_IN), U2.7 (VREG), U2.10 (VBAT), U2.11 (VBAT_IO), U2.24 (VR_PA), U4.2 (VO)
VDD_SPI: C12.1, C13.1, U1.29 (VDD_SPI), U5.8 (VCC)
